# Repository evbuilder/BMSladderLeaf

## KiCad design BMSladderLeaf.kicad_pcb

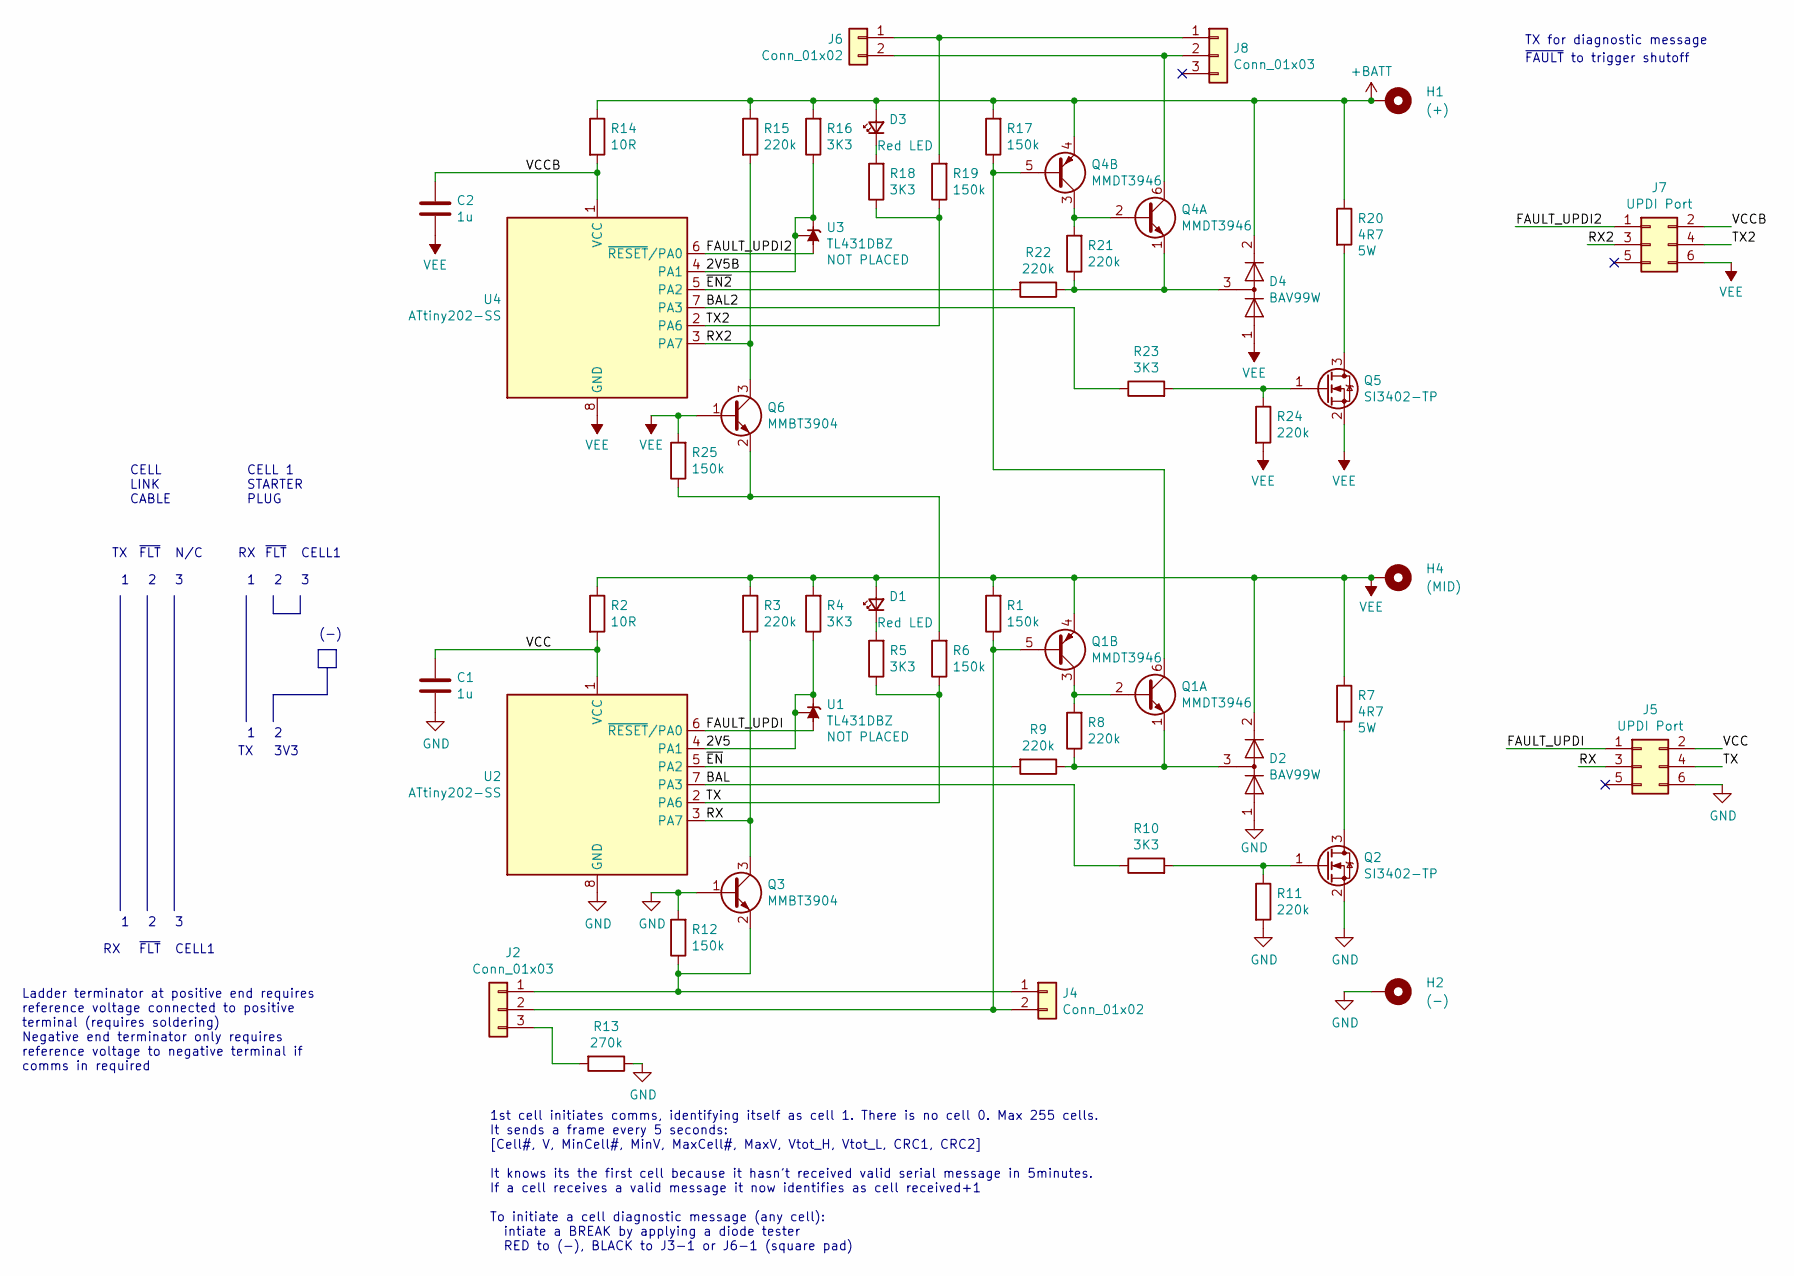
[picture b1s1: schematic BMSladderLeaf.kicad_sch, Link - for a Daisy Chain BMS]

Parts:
C1, C2: 1u; C_0603_1608Metric
D1, D3: Red LED; LED_0603_1608Metric
D2, D4: BAV99W; SOT-323_SC-70
H1: (+); Terminal tag 6.2mm slot
H2: (-); Terminal tag 6.2mm slot
H4: (MID); MountingHole_4.3mm_M4_Pad_Via
J2, J8: Conn_01x03; JST_SH_SM03B-SRSS-TB_1x03-1MP_P1.00mm_Horizontal
J4, J6: Conn_01x02; PinHeader_1x02_P2.00mm_Vertical
J5, J7: UPDI Port; PinHeader_2x03_P1.27mm_Vertical
Q1, Q4: MMDT3946; SOT-363_SC-70-6
Q2, Q5: SI3402-TP; SOT-23
Q3, Q6: MMBT3904; SOT-23
R1, R6, R12, R17, R19, R25: 150k; R_0603_1608Metric
R2, R14: 10R; R_0603_1608Metric
R3, R8, R9, R11, R15, R21, R22, R24: 220k; R_0603_1608Metric
R4, R5, R10, R16, R18, R23: 3K3; R_0603_1608Metric
R7, R20: 4R7; R_Axial_L17.0mm_D6.0mm_P22mm_Horizontal
R13: 270k; R_0603_1608Metric
U1, U3: TL431DBZ; SOT-23
U2, U4: ATtiny202-SS; SOIC-8_3.9x4.9mm_P1.27mm

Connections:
+BATT: D3.2 (A), D4.2 (A), H1.1, Q4.4 (E2), R14.1, R15.1, R16.2, R17.2, R20.1
/2V5: R4.1, U1.1 (K), U1.2 (REF), U2.4 (PA1)
/2V5B: R16.1, U3.1 (K), U3.2 (REF), U4.4 (PA1)
/BAL: R10.1, U2.7 (PA3)
/BAL2: R23.1, U4.7 (PA3)
/FAULT_UPDI: J5.1, U1.3 (A), U2.6 (~RESET/PA0)
/FAULT_UPDI2: J7.1, U3.3 (A), U4.6 (~RESET/PA0)
/RX: J5.3, Q3.3 (C), R3.2, U2.3 (PA7)
/RX2: J7.3, Q6.3 (C), R15.2, U4.3 (PA7)
/TX: J5.4, R5.1, R6.1, U2.2 (PA6)
/TX2: J7.4, R18.1, R19.1, U4.2 (PA6)
/VCC: C1.1, J5.2, R2.2, U2.1 (VCC)
/VCCB: C2.1, J7.2, R14.2, U4.1 (VCC)
/~EN2: R22.2, U4.5 (PA2)
/~EN: R9.2, U2.5 (PA2)
GND: C1.2, D2.1 (K), H2.1, J5.6, Q2.2 (S), Q3.1 (B), R11.2, R12.2, R13.1, U2.8 (GND)
unnamed: D1.1 (K), R5.2
unnamed: D3.1 (K), R18.2
unnamed: J2.1, J4.1, Q3.2 (E), R12.1
unnamed: J2.2, J4.2, Q1.5 (B2), R1.1
unnamed: J2.3, R13.2
unnamed: J6.1, J8.1, R19.2
unnamed: J6.2, J8.2, Q4.6 (C1)
unnamed: Q1.2 (B1), Q1.3 (C2), R8.2
unnamed: Q1.6 (C1), Q4.5 (B2), R17.1
unnamed: D2.3 (K), Q1.1 (E1), R8.1, R9.1
unnamed: Q2.3 (D), R7.2
unnamed: Q2.1 (G), R10.2, R11.1
unnamed: Q4.2 (B1), Q4.3 (C2), R21.2
unnamed: D4.3 (K), Q4.1 (E1), R21.1, R22.1
unnamed: Q5.3 (D), R20.2
unnamed 31: Q5.1 (G), R23.2, R24.1; also elsewhere on the board
unnamed: Q6.2 (E), R6.2, R25.1
VEE: C2.2, D1.2 (A), D2.2 (A), D4.1 (K), H4.1, J7.6, Q1.4 (E2), Q5.2 (S), Q6.1 (B), R1.2, R2.1, R3.1, R4.2, R7.1, R24.2, R25.2, U4.8 (GND); also elsewhere on the board

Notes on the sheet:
CELL1
~{FAULT} to trigger shutoff
CELL 1 STARTER PLUG
Ladder terminator at positive end requires reference voltage connected to positive terminal (requires soldering) Negative end terminator only requires reference voltage to negative terminal if comms in required
1st cell initiates comms, identifying itself as cell 1. There is no cell 0. Max 255 cells. It sends a frame every 5 seconds: [Cell#, V, MinCell#, MinV, MaxCell#, MaxV, Vtot_H, Vtot_L, CRC1, CRC2] It knows its the first cell because it hasn’t received valid serial message in 5minutes. If a cell rece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
~{FLT}
N/C
3V3
TX for diagnostic message
CELL LINK CABLE
(-)

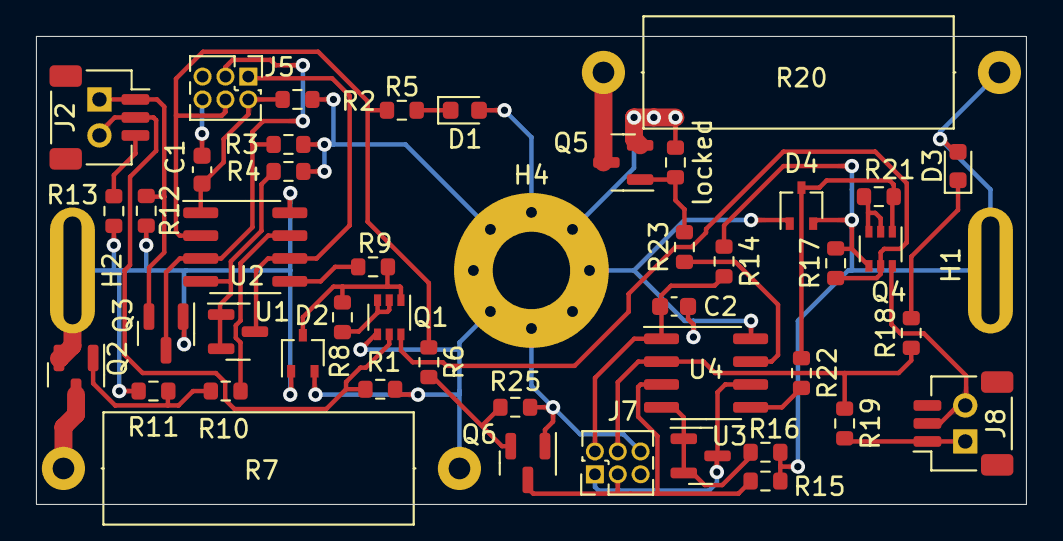
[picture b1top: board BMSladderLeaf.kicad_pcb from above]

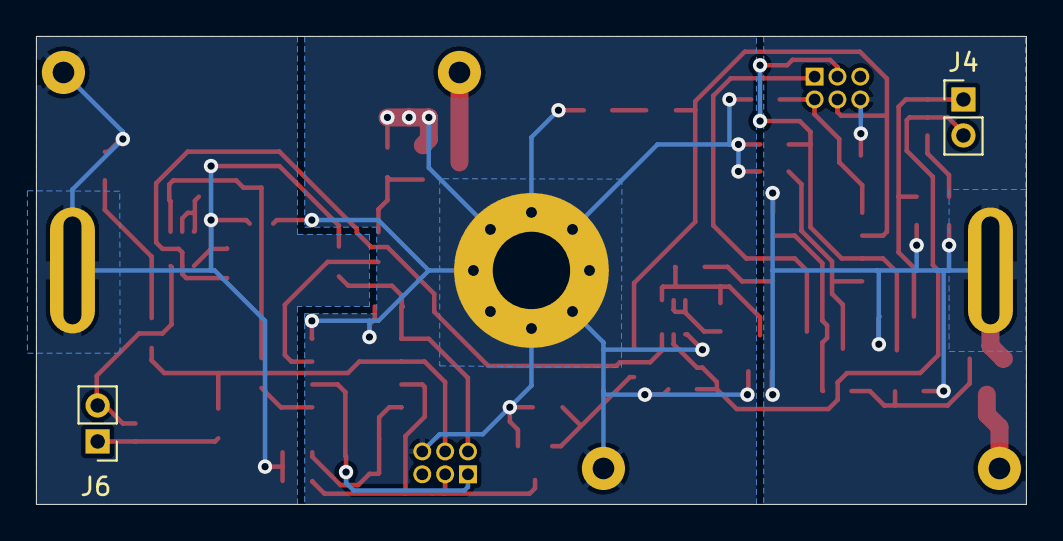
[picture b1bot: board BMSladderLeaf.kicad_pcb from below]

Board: 2 copper layers, 55.0 x 26.0 mm, 50 parts (2 on the bottom side), 34 nets.

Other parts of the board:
locked: 220k; R_0603_1608Metric

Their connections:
unnamed 31: locked.1; also elsewhere on the board
VEE: locked.2; also elsewhere on the board

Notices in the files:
BMSladderLeaf.kicad_pcb:
REV 1.1 (c) 2024 EHC
